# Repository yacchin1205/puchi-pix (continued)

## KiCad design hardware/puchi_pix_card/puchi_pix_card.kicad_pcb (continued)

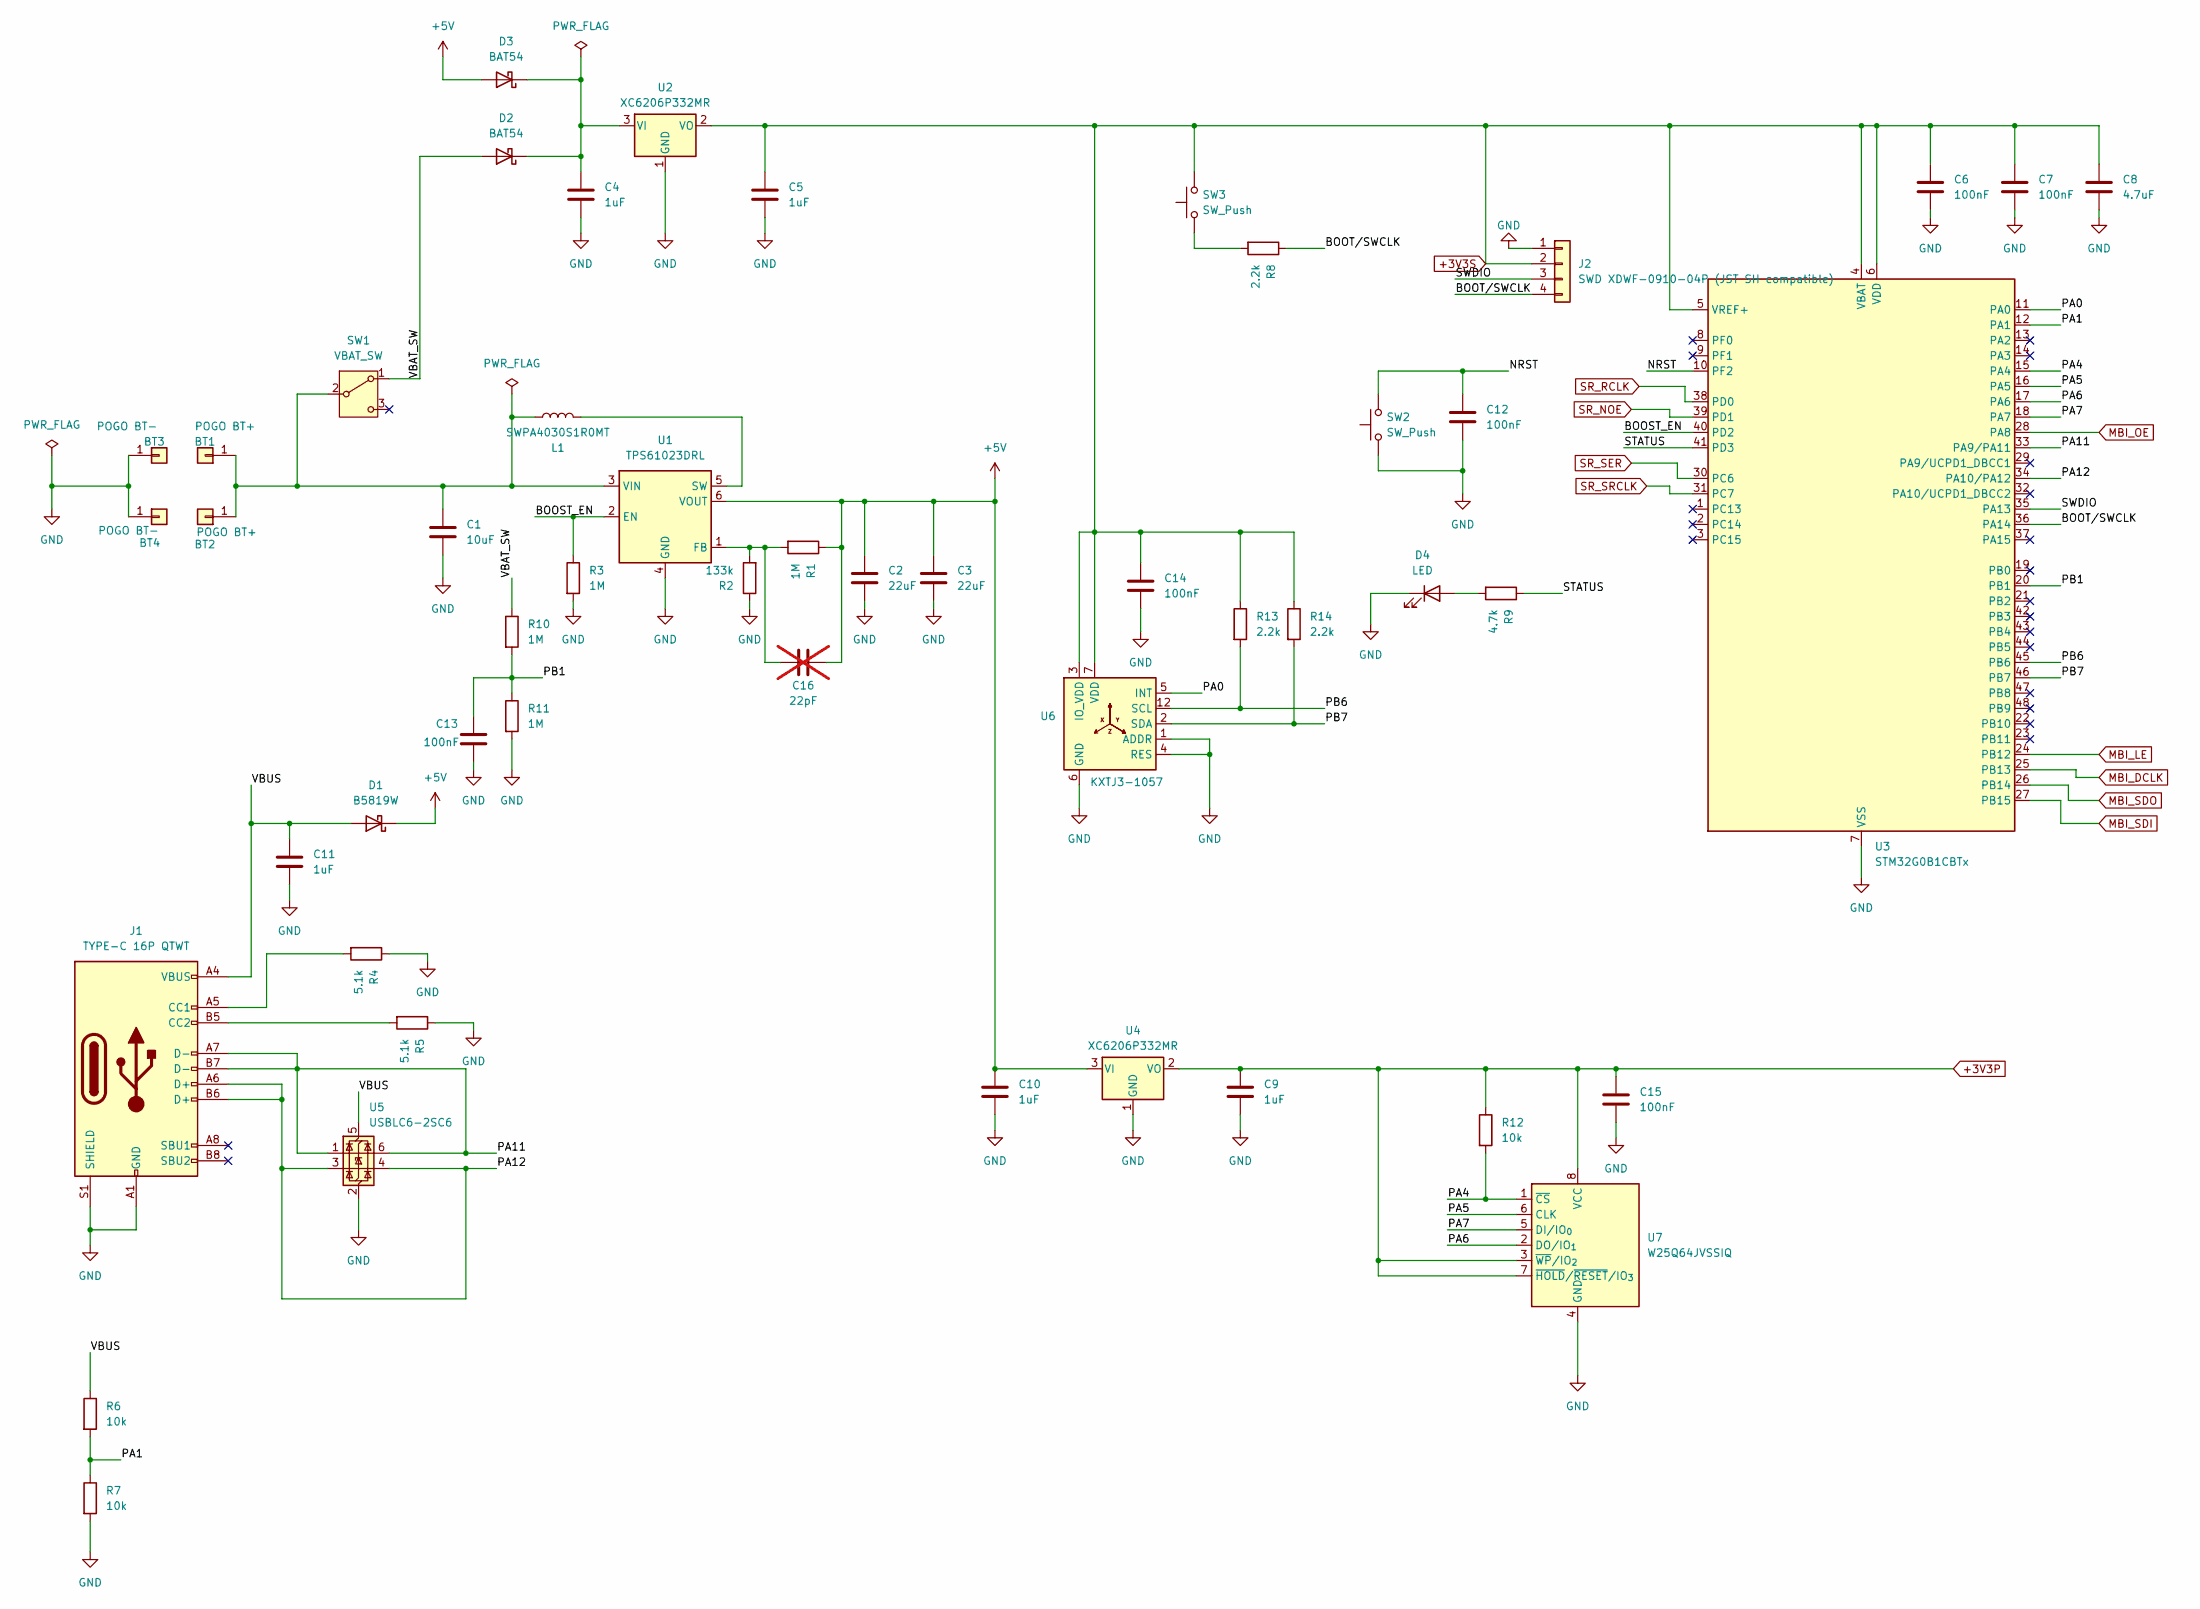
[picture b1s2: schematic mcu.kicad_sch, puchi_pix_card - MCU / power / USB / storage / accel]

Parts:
BT1, BT2: POGO BT+; Pogo_YTC1P_D2.0; LCSC C5221292
BT3, BT4: POGO BT-; Pogo_YTC1P_D2.0; LCSC C5221292
C1: 10uF; C_0805_2012Metric; LCSC C380332
C2, C3: 22uF; C_0805_2012Metric; LCSC C45783
C4, C5, C9, C10, C11: 1uF; C_0402_1005Metric; LCSC C52923
C6, C7, C12, C13, C14, C15: 100nF; C_0402_1005Metric; LCSC C309458
C8: 4.7uF; C_0402_1005Metric; LCSC C23733
C16: 22pF; C_0402_1005Metric; LCSC C1555; not fitted
D1: B5819W; D_SOD-123; LCSC C8598
D2, D3: BAT54; D_SOD-323; LCSC C22629
D4: LED; LED_0603_1608Metric; LCSC C12624
J1: TYPE-C 16P QTWT; USB_C_Receptacle_SHOUHAN_TYPE-C-16P-QTWT; LCSC C5187472
J2: SWD XDWF-0910-04P (JST SH compatible); JST_SH_SM04B-SRSS-TB_1x04-1MP_P1.00mm_Horizontal; LCSC C7527619
L1: SWPA4030S1R0MT; L_SWPA4030S; LCSC C316359
R1, R3, R10, R11: 1M; R_0402_1005Metric; LCSC C26083
R2: 133k; R_0402_1005Metric; LCSC C25753
R4, R5: 5.1k; R_0402_1005Metric; LCSC C25905
R6, R7, R12: 10k; R_0402_1005Metric; LCSC C25744
R8, R13, R14: 2.2k; R_0402_1005Metric; LCSC C25879
R9: 4.7k; R_0402_1005Metric; LCSC C25900
SW1: VBAT_SW; SW-SMD_MST-12D18G4-SPDT-SLIDE-SWITCH; LCSC C49023767
SW2, SW3: SW_Push; KEY-SMD_4P-L4.2-W3.2-P2.20-LS4.6; LCSC C139797
U1: TPS61023DRL; SOT-563; LCSC C919459
U2, U4: XC6206P332MR; SOT-23-3; LCSC C5446
U3: STM32G0B1CBTx; LQFP-48_7x7mm_P0.5mm; LCSC C2847904
U5: USBLC6-2SC6; SOT-23-6; LCSC C7519
U6: KXTJ3-1057; Kionix_LGA-12_2x2mm_P0.5mm_LayoutBorder2x4y; LCSC C442603
U7: W25Q64JVSSIQ; SOIC-8_5.3x5.3mm_P1.27mm; LCSC C179171

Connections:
+3V3P: C9.1, C15.1, R12.1, U4.2 (VO), U7.3 (~WP/IO_{2}), U7.7 (~HOLD/~RESET/IO_{3}), U7.8 (VCC); also elsewhere on the board
+3V3S: C5.1, C6.1, C7.1, C8.1, C14.1, J2.2, R13.1, R14.1, SW3.2, U2.2 (VO), U3.4 (VBAT), U3.5 (VREF+), U3.6 (VDD), U6.3 (IO_VDD), U6.7 (VDD), U6.10 (VDD), U6.11 (IO_VDD)
+5V: C2.1, C3.1, C10.1, C16.2, D1.1 (K), D3.2 (A), R1.1, U1.6 (VOUT), U4.3 (VI); also elsewhere on the board
/mcu/BOOST_EN: R3.1, U1.2 (EN), U3.40 (PD2)
/mcu/BOOT/SWCLK: J2.4, R8.1, U3.36 (PA14)
/mcu/NRST: C12.1, SW2.2, U3.10 (PF2)
/mcu/PA0: U3.11 (PA0), U6.5 (INT)
/mcu/PA1: R6.2, R7.1, U3.12 (PA1)
/mcu/PA4: R12.2, U3.15 (PA4), U7.1 (~CS)
/mcu/PA5: U3.16 (PA5), U7.6 (CLK)
/mcu/PA6: U3.17 (PA6), U7.2 (DO/IO_{1})
/mcu/PA7: U3.18 (PA7), U7.5 (DI/IO_{0})
/mcu/PA11: J1.A7 (D-), J1.B7 (D-), U3.33 (PA9/PA11), U5.1 (I/O1), U5.6 (I/O1)
/mcu/PA12: J1.A6 (D+), J1.B6 (D+), U3.34 (PA10/PA12), U5.3 (I/O2), U5.4 (I/O2)
/mcu/PB1: C13.1, R10.2, R11.1, U3.20 (PB1)
/mcu/PB6: R13.2, U3.45 (PB6), U6.12 (SCL)
/mcu/PB7: R14.2, U3.46 (PB7), U6.2 (SDA)
/mcu/STATUS: R9.1, U3.41 (PD3)
/mcu/SWDIO: J2.3, U3.35 (PA13)
/mcu/VBAT_SW: D2.2 (A), R10.1, SW1.1 (A)
/mcu/VBUS: C11.1, D1.2 (A), J1.A4 (VBUS), J1.A9 (VBUS), J1.B4 (VBUS), J1.B9 (VBUS), R6.1, U5.5 (VBUS)
GND: BT3.1, BT4.1, C1.2, C2.2, C3.2, C4.2, C5.2, C6.2, C7.2, C8.2, C9.2, C10.2, C11.2, C12.2, C13.2, C14.2, C15.2, D4.1 (K), J1.A1 (GND), J1.A12 (GND), J1.B1 (GND), J1.B12 (GND), J1.S1 (SHIELD), J2.1, R2.1, R3.2, R4.1, R5.1, R7.2, R11.2, SW2.1, U1.4 (GND), U2.1 (GND), U3.7 (VSS), U4.1 (GND), U5.2 (GND), U6.1 (ADDR), U6.4 (RES), U6.6 (GND), U6.8 (GND), U6.9 (GND), U7.4 (GND); also elsewhere on the board
MBI_DCLK: U3.25 (PB13); also elsewhere on the board
MBI_LE: U3.24 (PB12); also elsewhere on the board
MBI_OE: U3.28 (PA8); also elsewhere on the board
MBI_SDI: U3.27 (PB15); also elsewhere on the board
MBI_SDO: U3.26 (PB14); also elsewhere on the board
unnamed: BT1.1, BT2.1, C1.1, L1.1, SW1.2 (B), U1.3 (VIN)
unnamed: C4.1, D2.1 (K), D3.1 (K), U2.3 (VI)
unnamed: D4.2 (A), R9.2
unnamed: J1.A5 (CC1), R4.2
unnamed: J1.B5 (CC2), R5.2
unnamed: R8.2, SW3.1
unnamed: C16.1, R1.2, R2.2, U1.1 (FB)
unnamed: L1.2, U1.5 (SW)
SR_NOE: U3.39 (PD1); also elsewhere on the board
SR_RCLK: U3.38 (PD0); also elsewhere on the board
SR_SER: U3.30 (PC6); also elsewhere on the board
SR_SRCLK: U3.31 (PC7); also elsewhere on the board

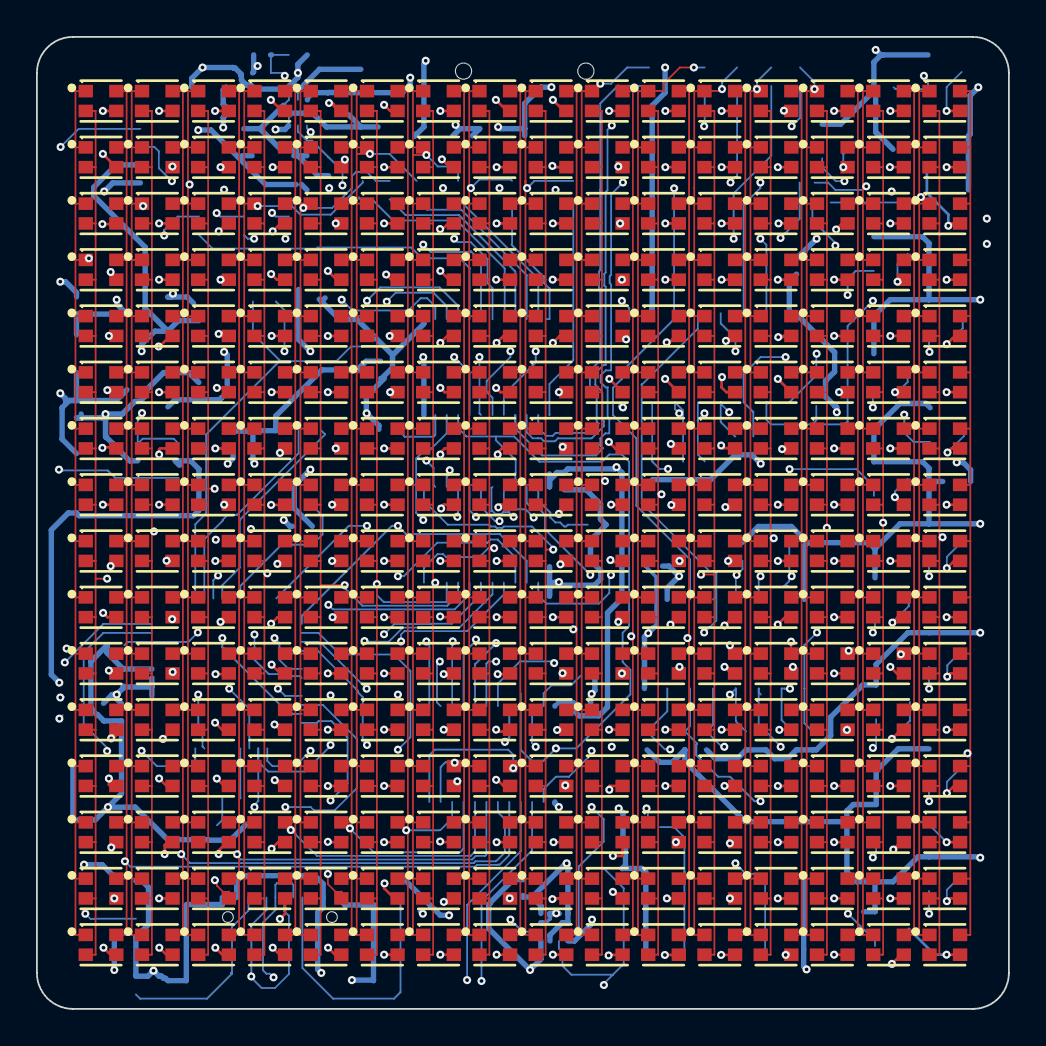
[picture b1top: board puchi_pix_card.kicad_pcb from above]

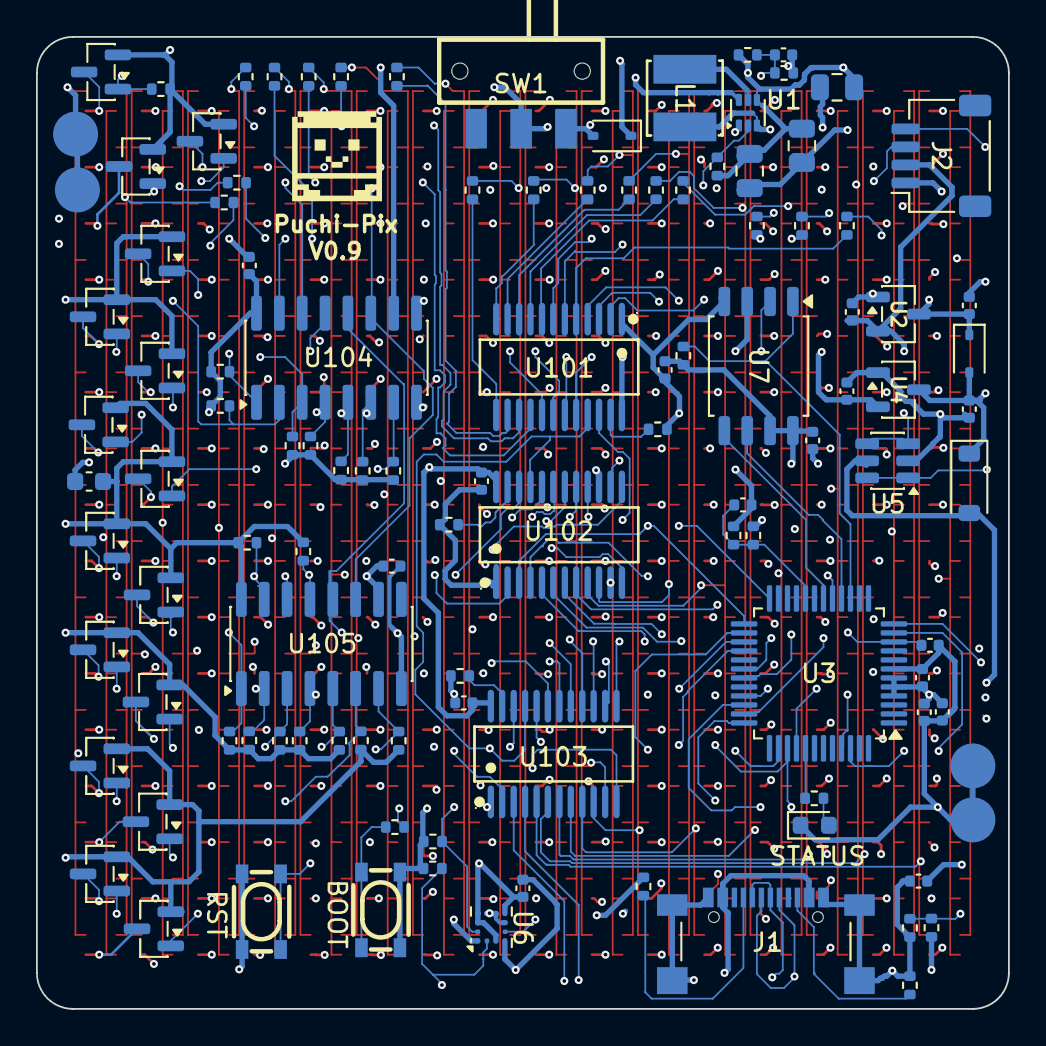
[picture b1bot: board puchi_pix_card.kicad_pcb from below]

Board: 4 copper layers, 54.0 x 54.0 mm, 371 parts (115 on the bottom side), 141 nets.

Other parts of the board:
LOGO1: puchi_pix_logo

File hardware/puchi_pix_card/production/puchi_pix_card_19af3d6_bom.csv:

Designator,Footprint,Quantity,Value,LCSC Part #
"BT1, BT2",Pogo_YTC1P_D2.0,2,POGO BT+,C5221292
"BT3, BT4",Pogo_YTC1P_D2.0,2,POGO BT-,C5221292
C1,0805,1,10uF,C380332
"C10, C11, C4, C5, C9",0402,5,1uF,C52923
"C101, C102, C103, C104, C105, C12, C13, C14, C15, C6, C7",0402,11,100nF,C309458
C106,0603,1,10uF,C96446
"C2, C3",0805,2,22uF,C45783
C8,0402,1,4.7uF,C23733
D1,D_SOD-123,1,B5819W,C8598
"D101, D102, D103, D104, D105, D106, D107, D108, D109, D110, D111, D112, D113, D114, D115, D116, D117, D118, D119, D120, D121, D122, D123, D124, D125, D126, D127, D128, D129, D130, D131, D132, D133, D134, D135, D136, D137, D138, D139, D140, D141, D142, D143, D144, D145, D146, D147, D148, D149, D150, D151, D152, D153, D154, D155, D156, D157, D158, D159, D160, D161, D162, D163, D164, D165, D166, D167, D168, D169, D170, D171, D172, D173, D174, D175, D176, D177, D178, D179, D180, D181, D182, D183, D184, D185, D186, D187, D188, D189, D190, D191, D192, D193, D194, D195, D196, D197, D198, D199, D200, D201, D202, D203, D204, D205, D206, D207, D208, D209, D210, D211, D212, D213, D214, D215, D216, D217, D218, D219, D220, D221, D222, D223, D224, D225, D226, D227, D228, D229, D230, D231, D232, D233, D234, D235, D236, D237, D238, D239, D240, D241, D242, D243, D244, D245, D246, D247, D248, D249, D250, D251, D252, D253, D254, D255, D256, D257, D258, D259, D260, D261, D262, D263, D264, D265, D266, D267, D268, D269, D270, D271, D272, D273, D274, D275, D276, D277, D278, D279, D280, D281, D282, D283, D284, D285, D286, D287, D288, D289, D290, D291, D292, D293, D294, D295, D296, D297, D298, D299, D300",LED_FM-B2020RGBA,200,FM-B2020RGBA-HG,C42421005
"D2, D3",D_SOD-323,2,BAT54,C22629
"D301, D302, D303, D304, D305, D306, D307, D308, D309, D310, D311, D312, D313, D314, D315, D316, D317, D318, D319, D320, D321, D322, D323, D324, D325, D326, D327, D328, D329, D330, D331, D332, D333, D334, D335, D336, D337, D338, D339, D340, D341, D342, D343, D344, D345, D346, D347, D348, D349, D350, D351, D352, D353, D354, D355, D356",LED_FM-B2020RGBA,56,FM-B2020RGBA-HG,C42421005
D4,0603,1,LED,C12624
J1,USB_C_Receptacle_SHOUHAN_TYPE-C-16P-QTWT,1,TYPE-C 16P QTWT,C5187472
J2,JST_SH_SM04B-SRSS-TB_1x04-1MP_P1.00mm_Horizontal,1,SWD XDWF-0910-04P (JST SH compatible),C7527619
L1,L_SWPA4030S,1,SWPA4030S1R0MT,C316359
"Q101, Q102, Q103, Q104, Q105, Q106, Q107, Q108, Q109, Q110, Q111, Q112, Q113, Q114, Q115, Q116",SOT-23,16,AO3401A,C15127
"R1, R10, R11, R3",0402,4,1M,C26083
R101,0402,1,2.0k,C4109
R102,0402,1,2.4k,C25882
"R103, R9",0402,2,4.7k,C25900
"R104, R12, R6, R7",0402,4,10k,C25744
"R105, R106, R107, R108, R109, R110, R111, R112, R113, R114, R115, R116, R117, R118, R119, R120",0402,16,120,C25079
"R121, R122, R123, R124, R125, R126, R127, R128, R129, R130, R131, R132, R133, R134, R135, R136",0402,16,100k,C25741
"R13, R14, R8",0402,3,2.2k,C25879
R2,0402,1,133k,C25753
"R4, R5",0402,2,5.1k,C25905
SW1,SW-SMD_MST-12D18G4-SPDT-SLIDE-SWITCH,1,VBAT_SW,C49023767
"SW2, SW3",KEY-SMD_4P-L4.2-W3.2-P2.20-LS4.6,2,SW_Push,C139797
U1,SOT-563,1,TPS61023DRL,C919459
U101,SSOP24L-150-0.64,1,MBI5124GP-B (R),C256866
U102,SSOP24L-150-0.64,1,MBI5124GP-B (G),C256866
U103,SSOP24L-150-0.64,1,MBI5124GP-B (B),C256866
"U104, U105",SOIC-16_3.9x9.9mm_P1.27mm,2,74HCT595,C282339
"U2, U4",SOT-23-3,2,XC6206P332MR,C5446
U3,LQFP-48_7x7mm_P0.5mm,1,STM32G0B1CBTx,C2847904
U5,SOT-23-6,1,USBLC6-2SC6,C7519
U6,Kionix_LGA-12_2x2mm_P0.5mm_LayoutBorder2x4y,1,KXTJ3-1057,C442603
U7,SOIC-8_5.3x5.3mm_P1.27mm,1,W25Q64JVSSIQ,C179171

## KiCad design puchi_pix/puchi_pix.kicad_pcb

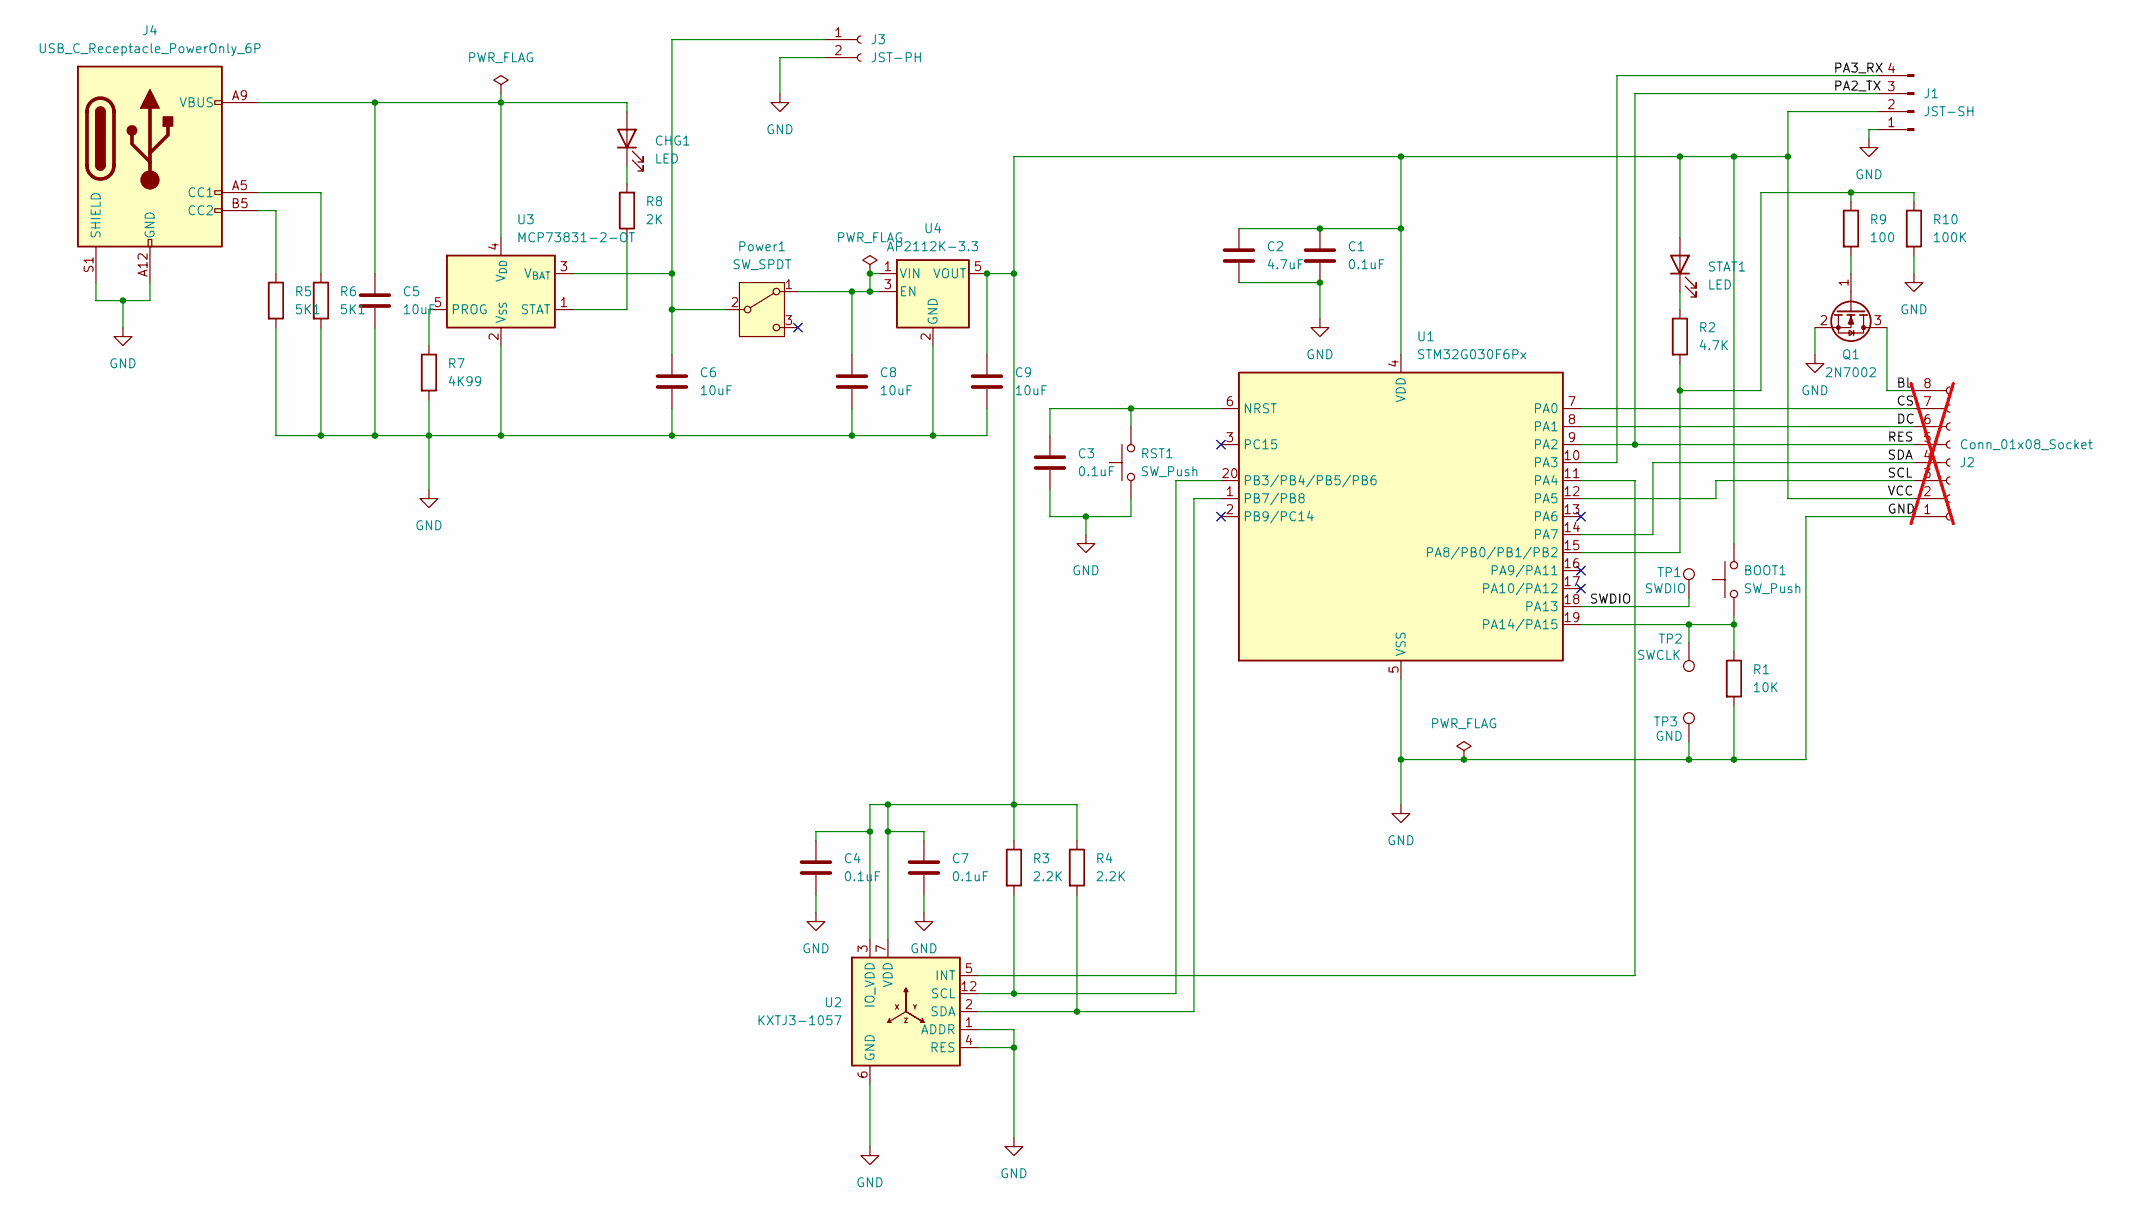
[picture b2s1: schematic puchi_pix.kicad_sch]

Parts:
BOOT1: SW_Push; KEY-SMD_4P-L4.2-W3.2-P2.20-LS4.6; LCSC C139797
C1, C3, C4, C7: 0.1uF; C_0402_1005Metric; LCSC C309458
C2: 4.7uF; C_0603_1608Metric; LCSC C19666
C5, C6, C8, C9: 10uF; C_0805_2012Metric; LCSC C380332
CHG1: LED; LED_0603_1608Metric; LCSC C2286
J1: JST-SH; JST_SH_SM04B-SRSS-TB_1x04-1MP_P1.00mm_Horizontal; LCSC C7527619
J2: Conn_01x08_Socket; PinSocket_1x08_P2.54mm_Vertical; not fitted
J3: JST-PH; JST_PH_S2B-PH-SM4-TB_1x02-1MP_P2.00mm_Horizontal; LCSC C968533
J4: USB_C_Receptacle_PowerOnly_6P; TYPE-C-SMD_TYPE-C-6P_1; LCSC C456012
Power1: SW_SPDT; SW-SMD_MST-12D18G4-SPDT-SLIDE-SWITCH; LCSC C49023767
Q1: 2N7002; SOT-23; LCSC C8545
R1: 10K; R_0402_1005Metric; LCSC C25744
R2: 4.7K; R_0402_1005Metric; LCSC C25900
R3, R4: 2.2K; R_0402_1005Metric; LCSC C25879
R5, R6: 5K1; R_0402_1005Metric; LCSC C25905
R7: 4K99; R_0402_1005Metric; LCSC C25903
R8: 2K; R_0402_1005Metric; LCSC C4109
R9: 100; R_0402_1005Metric; LCSC C25076
R10: 100K; R_0402_1005Metric; LCSC C25741
RST1: SW_Push; KEY-SMD_4P-L4.2-W3.2-P2.20-LS4.6; LCSC C139797
STAT1: LED; LED_0603_1608Metric; LCSC C12624
TP1: SWDIO; TestPoint_THTPad_D1.0mm_Drill0.5mm
TP2: SWCLK; TestPoint_THTPad_D1.0mm_Drill0.5mm
TP3: GND; TestPoint_THTPad_D1.0mm_Drill0.5mm
U1: STM32G030F6Px; TSSOP-20_4.4x6.5mm_P0.65mm; LCSC C724040
U2: KXTJ3-1057; Kionix_LGA-12_2x2mm_P0.5mm_LayoutBorder2x4y; LCSC C442603
U3: MCP73831-2-OT; SOT-23-5; LCSC C424093
U4: AP2112K-3.3; SOT-23-5; LCSC C51118

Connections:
/BL: J2.8, Q1.3 (D)
/CS: J2.7, U1.7 (PA0)
/DC: J2.6, U1.8 (PA1)
/PA2_TX: J1.3, J2.5, U1.9 (PA2)
/PA3_RX: J1.4, U1.10 (PA3)
/SCL: J2.3, U1.12 (PA5)
/SDA: J2.4, U1.14 (PA7)
/SWDIO: TP1.1, U1.18 (PA13)
/VCC: BOOT1.2, C1.1, C2.1, C4.1, C7.1, C9.1, J1.2, J2.2, R3.1, R4.1, STAT1.2 (A), U1.4 (VDD), U2.3 (IO_VDD), U2.7 (VDD), U2.10 (VDD), U2.11 (IO_VDD), U4.5 (VOUT)
GND: C1.2, C2.2, C3.2, C4.2, C5.2, C6.2, C7.2, C8.2, C9.2, J1.1, J2.1, J3.2, J4.A12 (GND), J4.B12 (GND), J4.S1 (SHIELD), Q1.2 (S), R1.2, R5.2, R6.2, R7.2, R10.2, RST1.1, TP3.1, U1.5 (VSS), U2.1 (ADDR), U2.4 (RES), U2.6 (GND), U2.8 (GND), U2.9 (GND), U3.2 (V_{SS}), U4.2 (GND)
unnamed: C5.1, CHG1.2 (A), J4.A9 (VBUS), J4.B9 (VBUS), U3.4 (V_{DD})
unnamed: CHG1.1 (K), R8.2
unnamed: C6.1, J3.1, Power1.2 (B), U3.3 (V_{BAT})
unnamed: J4.A5 (CC1), R6.1
unnamed: J4.B5 (CC2), R5.1
unnamed: C8.1, Power1.1 (A), U4.1 (VIN), U4.3 (EN)
unnamed: Q1.1 (G), R9.2
unnamed: R2.1, STAT1.1 (K)
unnamed: C3.1, RST1.2, U1.6 (NRST)
unnamed: U1.11 (PA4), U2.5 (INT)
unnamed: R2.2, R9.1, R10.1, U1.15 (PA8/PB0/PB1/PB2)
unnamed: BOOT1.1, R1.1, TP2.1, U1.19 (PA14/PA15)
unnamed: R3.2, U1.20 (PB3/PB4/PB5/PB6), U2.12 (SCL)
unnamed: R4.2, U1.1 (PB7/PB8), U2.2 (SDA)
unnamed: R7.1, U3.5 (PROG)
unnamed: R8.1, U3.1 (STAT)

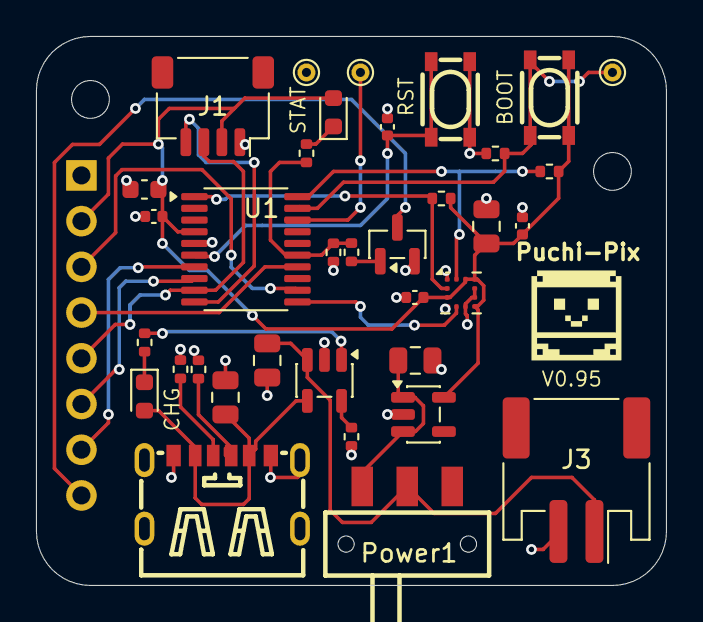
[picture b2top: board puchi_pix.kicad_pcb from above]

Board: 2 copper layers, 35.0 x 30.5 mm, 36 parts (1 on the bottom side), 26 nets.

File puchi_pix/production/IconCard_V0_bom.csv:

Designator,Footprint,Quantity,Value,LCSC Part #
"BOOT1, RST1",KEY-SMD_4P-L4.2-W3.2-P2.20-LS4.6,2,SW_Push,C139797
"C1, C3, C4, C7",0402,4,0.1uF,C309458
C2,0603,1,4.7uF,C19666
"C5, C6, C8, C9",0805,4,10uF,C380332
CHG1,0603,1,LED,C2286
J1,JST_SH_SM04B-SRSS-TB_1x04-1MP_P1.00mm_Horizontal,1,JST-SH,C7527619
J3,JST_PH_S2B-PH-SM4-TB_1x02-1MP_P2.00mm_Horizontal,1,JST-PH,C968533
J4,TYPE-C-SMD_TYPE-C-6P_1,1,USB_C_Receptacle_PowerOnly_6P,C456012
POWER1,SW-SMD_MST-12D18G4-SPDT-SLIDE-SWITCH,1,SW_SPDT,C49023767
R1,0402,1,10K,C25744
"R2, R8",0402,2,2K,C4109
"R3, R4",0402,2,2.2K,C25879
"R5, R6",0402,2,5K1,C25905
R7,0402,1,4K99,C25903
STAT1,0603,1,LED,C12624
U1,TSSOP-20_4.4x6.5mm_P0.65mm,1,STM32G030F6Px,C724040
U2,Kionix_LGA-12_2x2mm_P0.5mm_LayoutBorder2x4y,1,KXTJ3-1057,C442603
U3,SOT-23-5,1,MCP73831-2-OT,C424093
U4,SOT-23-5,1,AP2112K-3.3,C51118

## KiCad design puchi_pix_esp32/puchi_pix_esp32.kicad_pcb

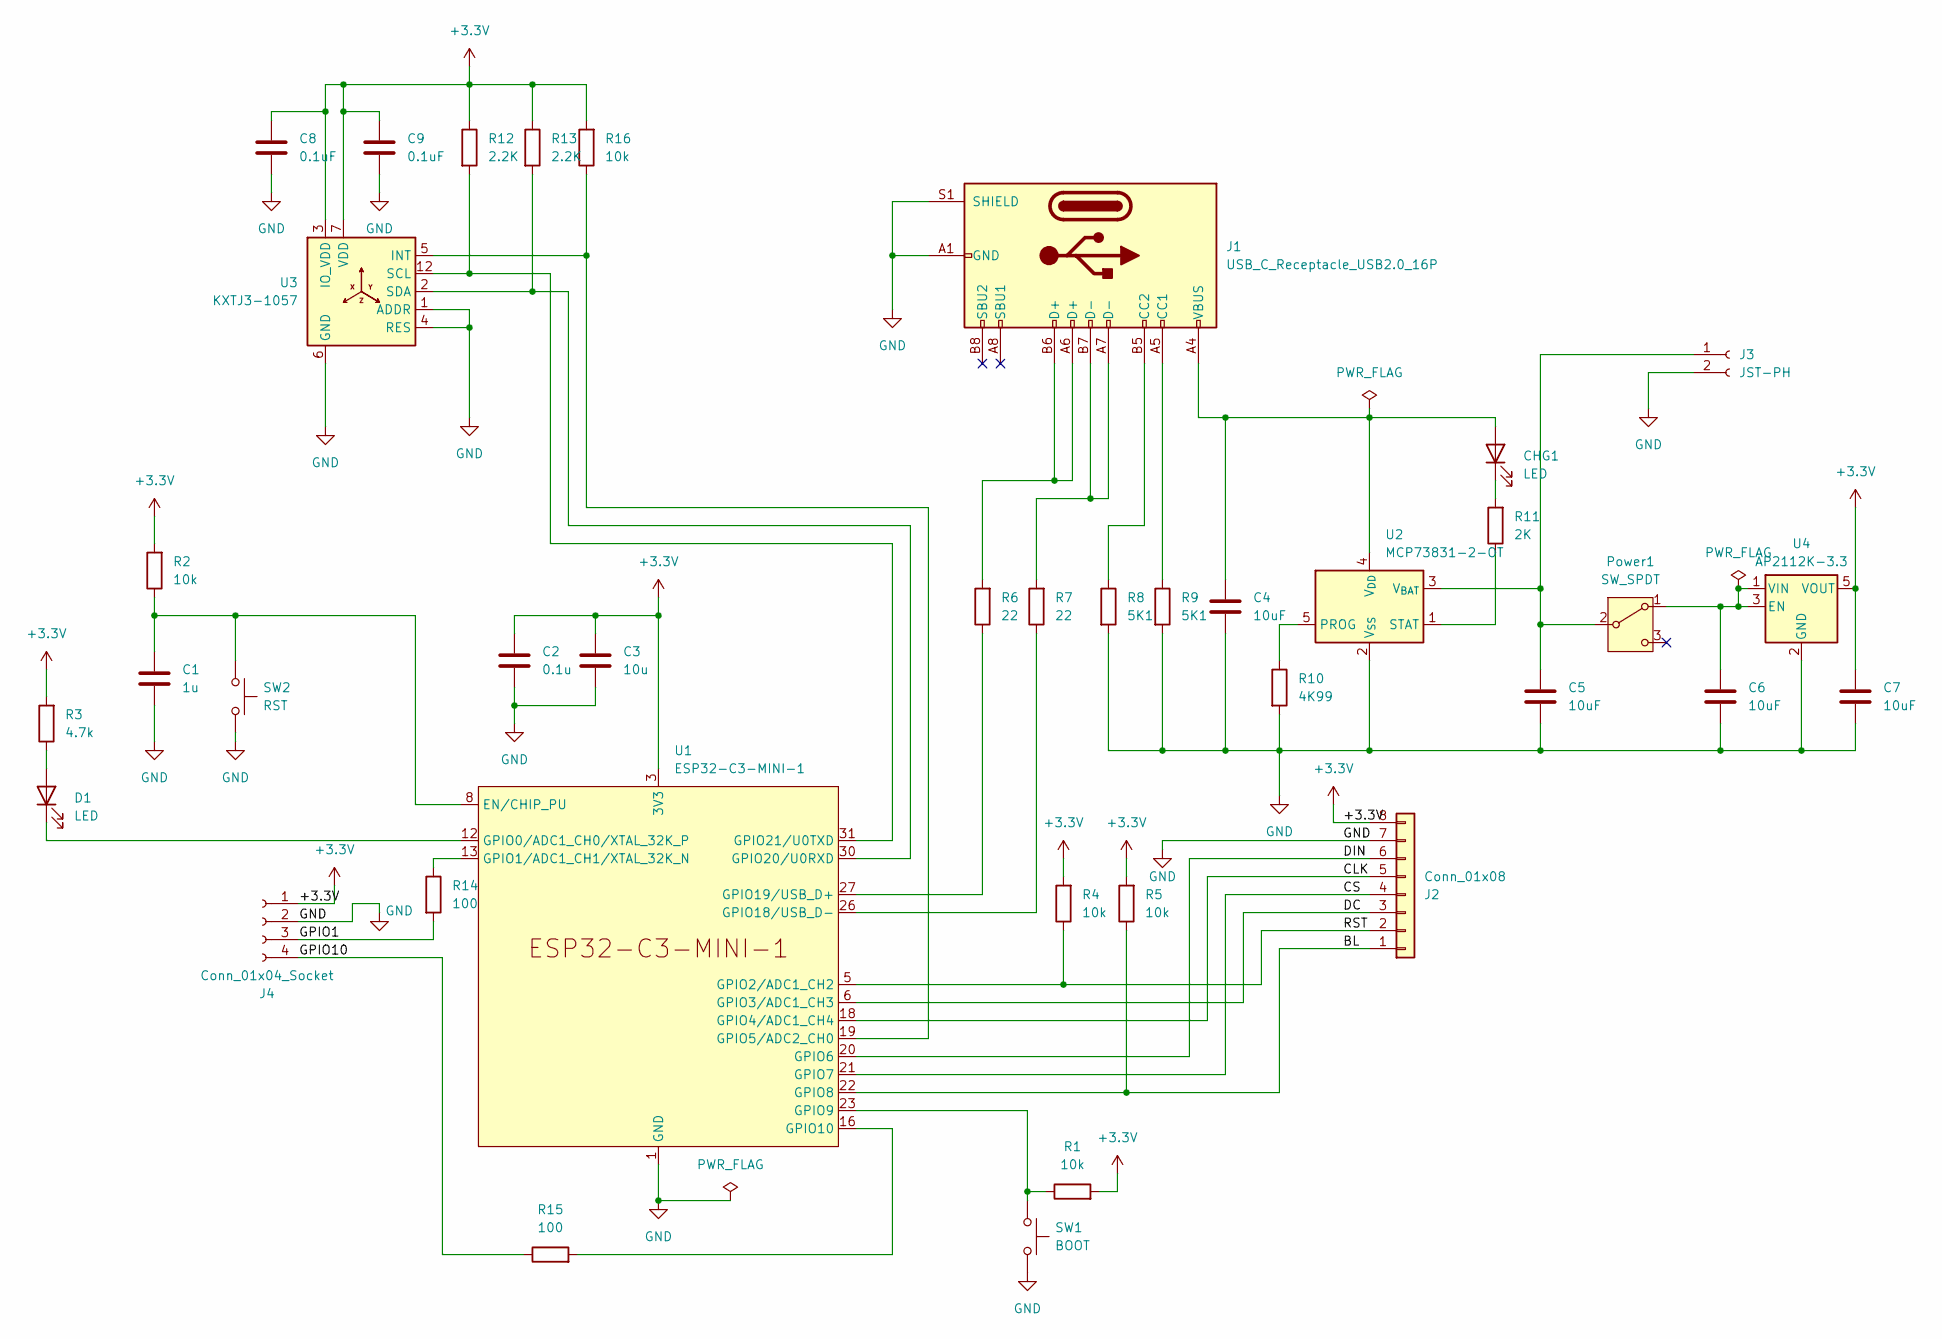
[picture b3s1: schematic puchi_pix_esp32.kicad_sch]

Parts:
C1: 1u; C_0402_1005Metric; LCSC C52923
C2: 0.1u; C_0402_1005Metric; LCSC C309458
C3: 10u; C_0805_2012Metric; LCSC C380332
C4, C5, C6, C7: 10uF; C_0805_2012Metric; LCSC C380332
C8, C9: 0.1uF; C_0402_1005Metric; LCSC C309458
CHG1: LED; LED_0603_1608Metric; LCSC C2286
D1: LED; LED_0603_1608Metric; LCSC C12624
J1: USB_C_Receptacle_USB2.0_16P; USB_C_Receptacle_HRO_TYPE-C-31-M-12; LCSC C165948
J2: Conn_01x08; JST_PH_S8B-PH-SM4-TB_1x08-1MP_P2.00mm_Horizontal; LCSC C265121
J3: JST-PH; JST_PH_S2B-PH-SM4-TB_1x02-1MP_P2.00mm_Horizontal; LCSC C968533
J4: Conn_01x04_Socket; PinSocket_1x04_P2.54mm_Vertical
Power1: SW_SPDT; SW-SMD_MST-12D18G4-SPDT-SLIDE-SWITCH; LCSC C49023767
R1, R2, R4, R5, R16: 10k; R_0402_1005Metric; LCSC C25744
R3: 4.7k; R_0402_1005Metric; LCSC C25900
R6, R7: 22; R_0402_1005Metric; LCSC C25092
R8, R9: 5K1; R_0402_1005Metric; LCSC C25905
R10: 4K99; R_0402_1005Metric; LCSC C25903
R11: 2K; R_0402_1005Metric; LCSC C4109
R12, R13: 2.2K; R_0402_1005Metric; LCSC C25879
R14, R15: 100; R_0402_1005Metric; LCSC C25076
SW1: BOOT; KEY-SMD_4P-L4.2-W3.2-P2.20-LS4.6; LCSC C139797
SW2: RST; KEY-SMD_4P-L4.2-W3.2-P2.20-LS4.6; LCSC C139797
U1: ESP32-C3-MINI-1; LCSC C2838502
U2: MCP73831-2-OT; SOT-23-5; LCSC C424093
U3: KXTJ3-1057; Kionix_LGA-12_2x2mm_P0.5mm_LayoutBorder2x4y; LCSC C442603
U4: AP2112K-3.3; SOT-23-5; LCSC C51118

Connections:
+3.3V: C2.1, C3.1, C7.1, C8.1, C9.1, J2.8, J4.1, R1.2, R2.2, R3.2, R4.2, R5.2, R12.1, R13.1, R16.2, U1.3 (3V3), U3.3 (IO_VDD), U3.7 (VDD), U3.10 (VDD), U3.11 (IO_VDD), U4.5 (VOUT)
/BL: J2.1, R5.1, U1.22 (GPIO8)
/CLK: J2.5, U1.18 (GPIO4/ADC1_CH4)
/CS: J2.4, U1.21 (GPIO7)
/DC: J2.3, U1.6 (GPIO3/ADC1_CH3)
/DIN: J2.6, U1.20 (GPIO6)
/GPIO1: J4.3, R14.2
/GPIO10: J4.4, R15.1
/RST: J2.2, R4.1, U1.5 (GPIO2/ADC1_CH2)
GND: C1.2, C2.2, C3.2, C4.2, C5.2, C6.2, C7.2, C8.2, C9.2, J1.A1 (GND), J1.A12 (GND), J1.B1 (GND), J1.B12 (GND), J1.S1 (SHIELD), J2.7, J3.2, J4.2, R8.2, R9.2, R10.2, SW1.2, SW2.2, U1.1 (GND), U1.2 (GND), U1.11 (GND), U1.14 (GND), U1.36 (GND), U1.37 (GND), U1.38 (GND), U1.39 (GND), U1.40 (GND), U1.41 (GND), U1.42 (GND), U1.43 (GND), U1.44 (GND), U1.45 (GND), U1.46 (GND), U1.47 (GND), U1.48 (GND), U1.49 (GND), U1.50 (GND), U1.51 (GND), U1.52 (GND), U1.53 (GND), U2.2 (V_{SS}), U3.1 (ADDR), U3.4 (RES), U3.6 (GND), U3.8 (GND), U3.9 (GND), U4.2 (GND)
unnamed: C4.1, CHG1.2 (A), J1.A4 (VBUS), J1.A9 (VBUS), J1.B4 (VBUS), J1.B9 (VBUS), U2.4 (V_{DD})
unnamed: CHG1.1 (K), R11.2
unnamed: D1.2 (A), R3.1
unnamed: D1.1 (K), U1.12 (GPIO0/ADC1_CH0/XTAL_32K_P)
unnamed: J1.A5 (CC1), R9.1
unnamed: J1.B5 (CC2), R8.1
unnamed: J1.A6 (D+), J1.B6 (D+), R6.2
unnamed: J1.A7 (D-), J1.B7 (D-), R7.2
unnamed: C5.1, J3.1, Power1.2 (B), U2.3 (V_{BAT})
unnamed: C6.1, Power1.1 (A), U4.1 (VIN), U4.3 (EN)
unnamed: C1.1, R2.1, SW2.1, U1.8 (EN/CHIP_PU)
unnamed: R14.1, U1.13 (GPIO1/ADC1_CH1/XTAL_32K_N)
unnamed: R16.1, U1.19 (GPIO5/ADC2_CH0), U3.5 (INT)
unnamed: R1.1, SW1.1, U1.23 (GPIO9)
unnamed: R15.2, U1.16 (GPIO10)
unnamed: R7.1, U1.26 (GPIO18/USB_D-)
unnamed: R6.1, U1.27 (GPIO19/USB_D+)
unnamed: R13.2, U1.30 (GPIO20/U0RXD), U3.2 (SDA)
unnamed: R12.2, U1.31 (GPIO21/U0TXD), U3.12 (SCL)
unnamed: R10.1, U2.5 (PROG)
unnamed: R11.1, U2.1 (STAT)

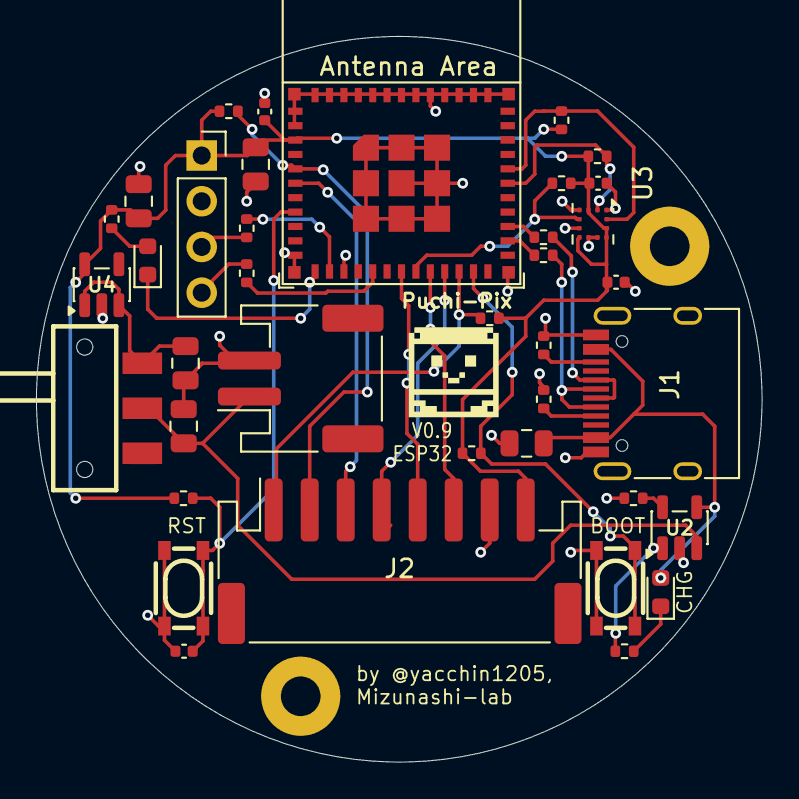
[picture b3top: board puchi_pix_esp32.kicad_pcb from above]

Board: 2 copper layers, 40.3 x 40.3 mm, 38 parts (0 on the bottom side), 31 nets.

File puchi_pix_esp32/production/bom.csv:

Designator,Footprint,Quantity,Value,LCSC Part #
C1,0402,1,1u,C52923
C2,0402,1,0.1u,C309458
C3,0805,1,10u,C380332
"C4, C5, C6, C7",0805,4,10uF,C380332
"C8, C9",0402,2,0.1uF,C309458
CHG1,0603,1,LED,C2286
D1,0603,1,LED,C12624
J1,USB_C_Receptacle_HRO_TYPE-C-31-M-12,1,USB_C_Receptacle_USB2.0_16P,C165948
J2,JST_PH_S8B-PH-SM4-TB_1x08-1MP_P2.00mm_Horizontal,1,Conn_01x08,C265121
J3,JST_PH_S2B-PH-SM4-TB_1x02-1MP_P2.00mm_Horizontal,1,JST-PH,C968533
POWER1,SW-SMD_MST-12D18G4-SPDT-SLIDE-SWITCH,1,SW_SPDT,C49023767
"R1, R16, R2, R4, R5",0402,5,10k,C25744
R10,0402,1,4K99,C25903
R11,0402,1,2K,C4109
"R12, R13",0402,2,2.2K,C25879
"R14, R15",0402,2,100,C25076
R3,0402,1,4.7k,C25900
"R6, R7",0402,2,22,C25092
"R8, R9",0402,2,5K1,C25905
SW1,KEY-SMD_4P-L4.2-W3.2-P2.20-LS4.6,1,BOOT,C139797
SW2,KEY-SMD_4P-L4.2-W3.2-P2.20-LS4.6,1,RST,C139797
U1,ESP32-C3-MINI-1,1,ESP32-C3-MINI-1,C2838502
U2,SOT-23-5,1,MCP73831-2-OT,C424093
U3,Kionix_LGA-12_2x2mm_P0.5mm_LayoutBorder2x4y,1,KXTJ3-1057,C442603
U4,SOT-23-5,1,AP2112K-3.3,C51118

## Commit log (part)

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2026-01-17 Fix timeout for sleep
2026-01-25 Add dummy data
2026-03-15 Add files for JLCPCB
2026-05-05 Scale GC9A01 puchi_pix icon 3x to 192x192 on 240x240 panel
2026-05-05 Add ESP32 enclosure Blender source (box-esp32.blend)
2026-05-05 Ignore STL/3MF exports under box/ and untrack existing STL/3MF files
2026-05-05 Update puchi-pix.psd source image
2026-05-05 Ignore *.kicad_prl (KiCad local UI state)
